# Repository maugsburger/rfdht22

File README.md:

rfdht22
=======

RF temp/hum sensor, grown from a DHT22 and NRF24L01p based sensor to something bigger.

Originally, I just wanted to monitor humidity and temperature in all rooms of my flat, submit them wireless to a master where you can read them out and get some other fancy features (eg close all windows, now it's warmer on the outside than inside).

sensor
------

With every step of hardware design, it grew a little bit bigger, so there are two different version right now:

- either a small headless version with dht22 or one-wire and i2c, powered by attiny2313a, as cheap as possible (single sided with some bridges)

- or a big version with lcd, twi/i2c, one-wire, quad direct analogue and quad opamp driven analogue in

One design goal was to make the sensors as power saving as possible, so they will hopefully run multiple years on a pair of AA cells. No wires, no problem with WAF.

master
------

Power doesn't matter here, big ass display (currently only 4x20 character LCD), can show values of all sensors, and a lot of planned features still in my head.

possible improvements
---------------------

 - lan interface for master
 - hack some radiator controller to enable remote control

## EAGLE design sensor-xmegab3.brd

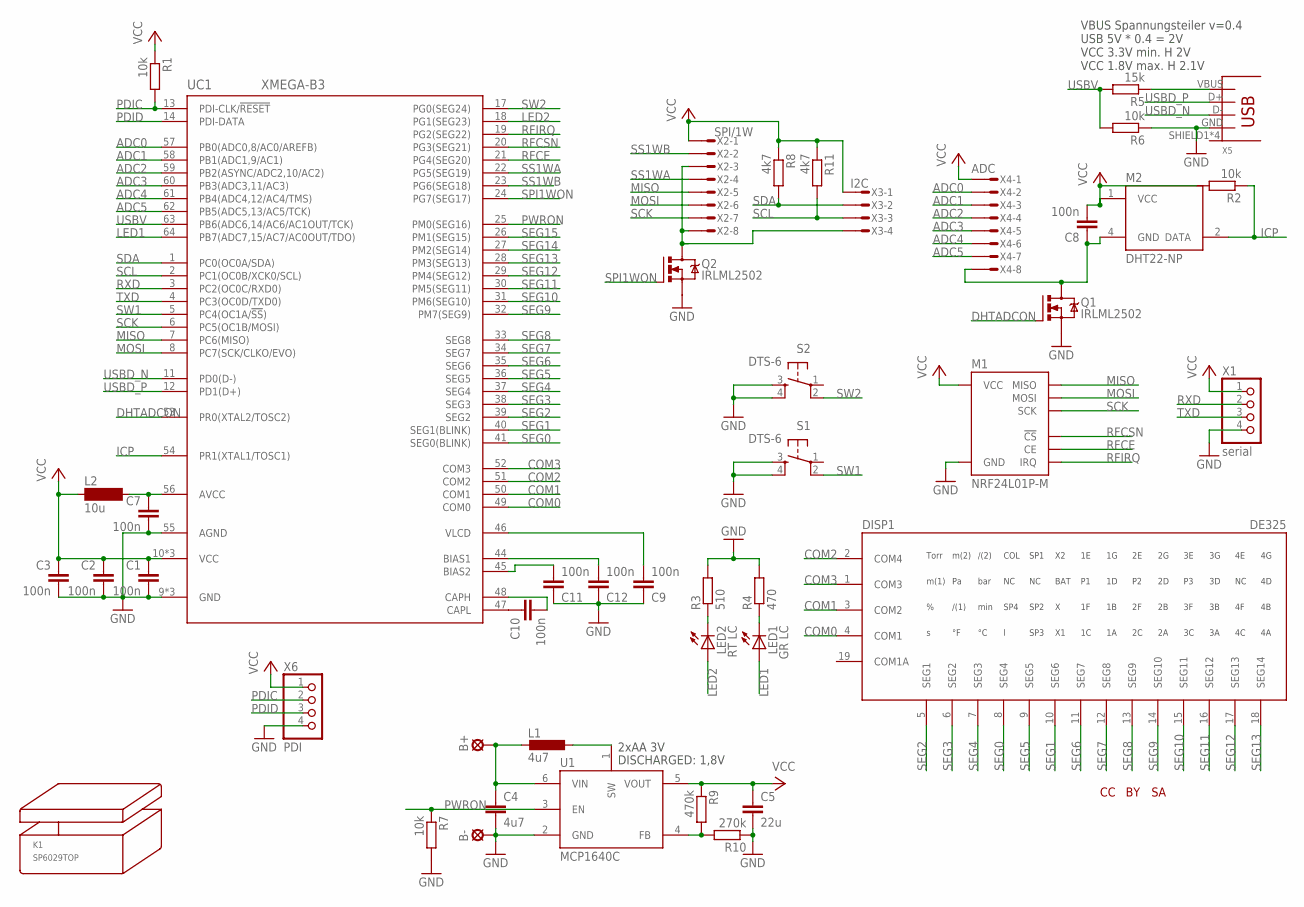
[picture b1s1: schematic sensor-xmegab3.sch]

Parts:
B+: LSP11
B-: LSP11
C1, C2, C3, C7, C8, C9, C10, C11, C12: 100n; C0603
C4: 4u7; C0805
C5: 22u; C1206
DISP1: DE325
K1: SP6029TOP; SP6029T
L1: 4u7; PISG
L2: 10u; SM-NE29
LED1: GR LC; LED5MM
LED2: RT LC; LED5MM
M1: NRF24L01P-M; NRF24L01P-A
M2: DHT22-NP; DHT22-NOPRINT
Q1, Q2: IRLML2502; MICRO3
R1, R2, R6, R7: 10k; R0603
R3: 510; R0805
R4: 470; R0805
R5: 15k; R0603
R8, R11: 4k7; R0603
R9: 470k; R0603
R10: 270k; R0603
S1, S2: DTS-6
U1: MCP1640C; SOT23-6
U$1: CC-TPLACE-HALF; CC_TPLACE_HS
U$3: BY-TPLACE-HS; BY_TPLACE_HS
U$4: SA-TPLACE-HALF; SA_TPLACE_HS
UC1: XMEGA-B3; TQFP64
X1: serial; 1X04
X2: SPI/1W; MICROMATCH-8
X3: I2C; MICROMATCH-4
X4: ADC; MICROMATCH-8
X5: USB; USB-MB-S
X6: PDI; 1X04

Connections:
ADC0: UC1.57 (PB0(ADC0,8/AC0/AREFB)), X4.2
ADC1: UC1.58 (PB1(ADC1,9/AC1)), X4.3
ADC2: UC1.59 (PB2(ASYNC/ADC2,10/AC2)), X4.4
ADC3: UC1.60 (PB3(ADC3,11/AC3)), X4.5
ADC4: UC1.61 (PB4(ADC4,12/AC4/TMS)), X4.6
ADC5: UC1.62 (PB5(ADC5,13/AC5/TCK)), X4.7
AVCC: C7.1, L2.2, UC1.56 (AVCC)
COM0: DISP1.4 (COM1), UC1.49 (COM0)
COM1: DISP1.3 (COM2), UC1.50 (COM1)
COM2: DISP1.2 (COM4), UC1.51 (COM2)
COM3: DISP1.1 (COM3), UC1.52 (COM3)
DHTADCON: Q1.1 (G), UC1.53 (PR0(XTAL2/TOSC2))
GND: B-.MP, C1.2, C2.2, C3.2, C4.2, C5.2, C7.2, C9.1, C11.1, C12.1, M1.GND_A (GND), M1.GND_B (GND), Q1.2 (S), Q2.2 (S), R3.2, R4.2, R6.1, R7.2, R10.1, S1.3, S1.4, S2.3, S2.4, U1.2 (GND), UC1.9 (GND), UC1.15 (GND), UC1.42 (GND), UC1.55 (AGND), X1.4, X5.GND, X6.4
ICP: M2.2 (DATA), R2.1, UC1.54 (PR1(XTAL1/TOSC1))
LED1: LED1.A, UC1.64 (PB7(ADC7,15/AC7/AC0OUT/TDO))
LED2: LED2.A, UC1.18 (PG1(SEG23))
MISO: M1.MISO, UC1.7 (PC6(MISO)), X2.5
MOSI: M1.MOSI, UC1.8 (PC7(SCK/CLKO/EVO)), X2.6
unnamed: LED1.K (C), R4.1
unnamed: R5.1, X5.VBUS
unnamed: LED2.K (C), R3.1
unnamed: L1.1, U1.1 (SW)
unnamed: R9.2, R10.2, U1.4 (FB)
unnamed: C11.2, UC1.45 (BIAS2)
unnamed: C12.2, UC1.44 (BIAS1)
unnamed: Q2.3 (D), X2.3, X2.8, X3.4
unnamed: C8.1, M2.4 (GND), Q1.3 (D), X4.8
unnamed: C9.2, UC1.46 (VLCD)
unnamed: C10.1, UC1.47 (CAPL)
unnamed: C10.2, UC1.48 (CAPH)
PDIC: R1.2, UC1.13 (PDI-CLK/!RESET), X6.2
PDID: UC1.14 (PDI-DATA), X6.3
PWRON: R7.1, U1.3 (EN), UC1.25 (PM0(SEG16))
RFCE: M1.CE, UC1.21 (PG4(SEG20))
RFCSN: M1.CSN (!CS), UC1.20 (PG3(SEG21))
RFIRQ: M1.IRQ, UC1.19 (PG2(SEG22))
RXD: UC1.3 (PC2(OC0C/RXD0)), X1.2
SCK: M1.SCK, UC1.6 (PC5(OC1B/MOSI)), X2.7
SCL: R11.2, UC1.2 (PC1(OC0B/XCK0/SCL)), X3.3
SDA: R8.2, UC1.1 (PC0(OC0A/SDA)), X3.2
SEG0: DISP1.8 (SEG4), UC1.41 (SEG0(BLINK))
SEG1: DISP1.10 (SEG6), UC1.40 (SEG1(BLINK))
SEG2: DISP1.5 (SEG1), UC1.39 (SEG2)
SEG3: DISP1.6 (SEG2), UC1.38 (SEG3)
SEG4: DISP1.7 (SEG3), UC1.37 (SEG4)
SEG5: DISP1.9 (SEG5), UC1.36 (SEG5)
SEG6: DISP1.11 (SEG7), UC1.35 (SEG6)
SEG7: DISP1.12 (SEG8), UC1.34 (SEG7)
SEG8: DISP1.13 (SEG9), UC1.33 (SEG8)
SEG9: DISP1.14 (SEG10), UC1.32 (PM7(SEG9))
SEG10: DISP1.15 (SEG11), UC1.31 (PM6(SEG10))
SEG11: DISP1.16 (SEG12), UC1.30 (PM5(SEG11))
SEG12: DISP1.17 (SEG13), UC1.29 (PM4(SEG12))
SEG13: DISP1.18 (SEG14), UC1.28 (PM3(SEG13))
SEG14: UC1.27 (PM2(SEG14))
SEG15: UC1.26 (PM1(SEG15))
SPI1WON: Q2.1 (G), UC1.24 (PG7(SEG17))
SS1WA: UC1.22 (PG5(SEG19)), X2.4
SS1WB: UC1.23 (PG6(SEG18)), X2.2
SW1: S1.2, UC1.5 (PC4(OC1A/!SS!))
SW2: S2.2, UC1.17 (PG0(SEG24))
TXD: UC1.4 (PC3(OC0D/TXD0)), X1.3
USBD_N: UC1.11 (PD0(D-)), X5.D-
USBD_P: UC1.12 (PD1(D+)), X5.D+
USBV: R5.2, R6.2, UC1.63 (PB6(ADC6,14/AC6/AC1OUT/TCK))
VBAT: B+.MP, C4.1, L1.2, U1.6 (VIN)
VCC: C1.1, C2.1, C3.1, C5.1, C8.2, L2.1, M1.VCC_A (VCC), M1.VCC_B (VCC), M2.1 (VCC), R1.1, R2.2, R8.1, R9.1, R11.1, U1.5 (VOUT), UC1.10 (VCC), UC1.16 (VCC), UC1.43 (VCC), X1.1, X2.1, X3.1, X4.1, X6.1

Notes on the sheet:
2xAA 3V
DISCHARGED: 1,8V
VBUS Spannungsteiler v=0.4 USB 5V * 0.4 = 2V VCC 3.3V min. H 2V VCC 1.8V max. H 2.1V

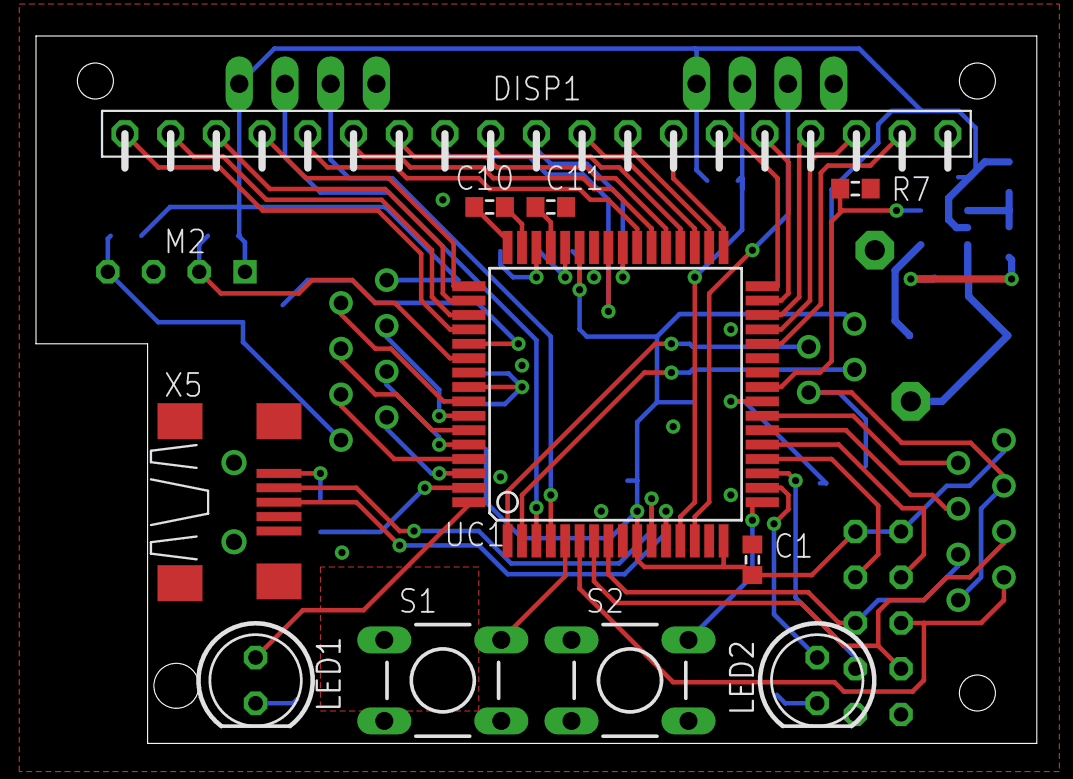
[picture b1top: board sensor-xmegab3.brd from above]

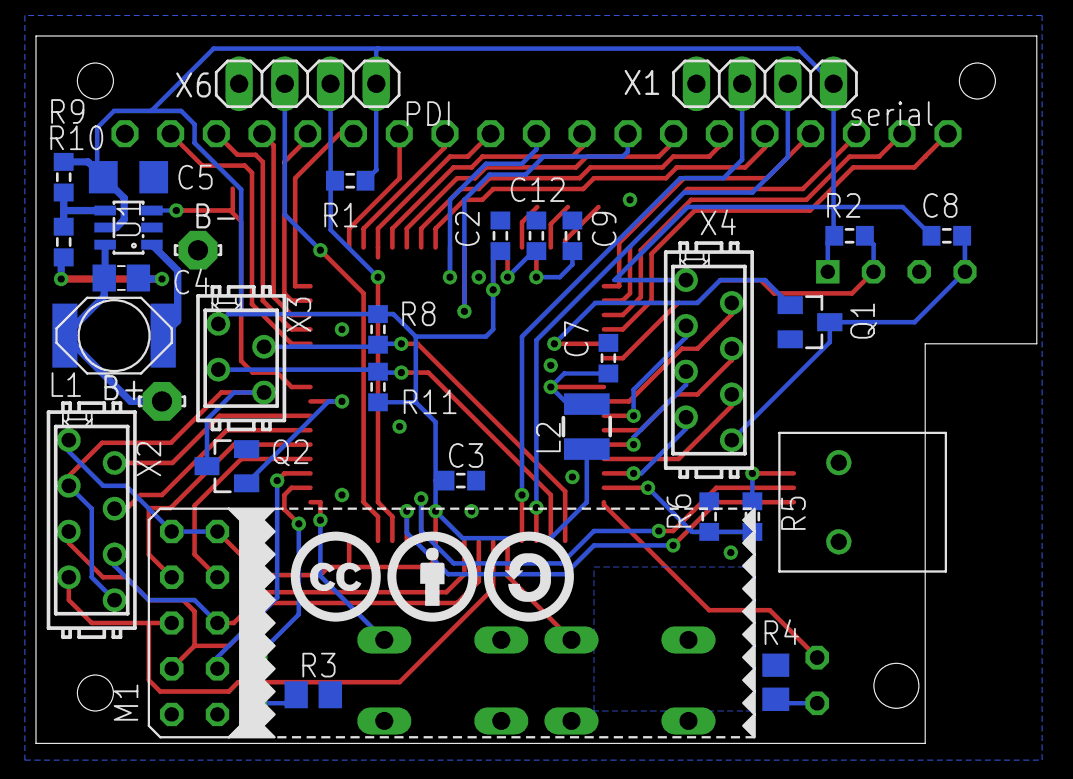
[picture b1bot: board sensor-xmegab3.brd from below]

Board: 2 copper layers, 55.6 x 39.3 mm, 47 parts (34 on the bottom side), 65 nets.

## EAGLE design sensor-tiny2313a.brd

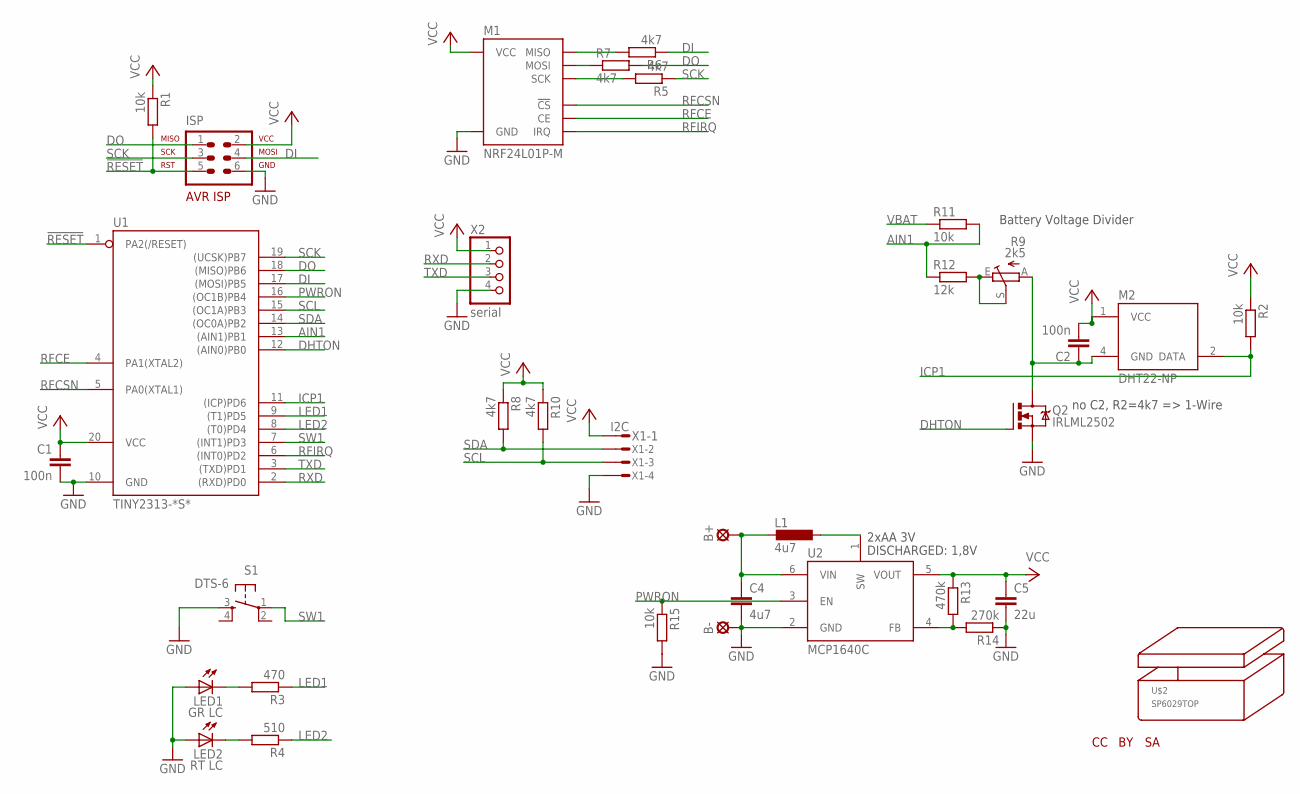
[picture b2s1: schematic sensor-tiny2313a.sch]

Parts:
B+: LSP11
B-: LSP11
C1, C2: 100n; C0603
C4: 4u7; C0805
C5: 22u; C1206
ISP: ML6; AVR-ISP-6
L1: 4u7; PISG
LED1: GR LC; LED5MM
LED2: RT LC; LED5MM
M1: NRF24L01P-M; NRF24L01P-A
M2: DHT22-NP; DHT22-NOPRINT
Q2: IRLML2502; MICRO3
R1, R2, R11, R15: 10k; R0603
R3: 470; R0603
R4: 510; R0603
R5, R6, R7, R8, R10: 4k7; R0603
R9: 2k5; CA6H
R12: 12k; R0603
R13: 470k; R0603
R14: 270k; R0603
S1: DTS-6
U1: TINY2313-*S*; SO20L$
U2: MCP1640C; SOT23-6
U$1: CC-TPLACE-HALF; CC_TPLACE_HS
U$2: SP6029TOP; SP6029T
U$3: BY-TPLACE-HS; BY_TPLACE_HS
U$4: SA-TPLACE-HALF; SA_TPLACE_HS
X1: I2C; MICROMATCH-4
X2: serial; 1X04

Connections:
!RESET: ISP.5, R1.2, U1.1 (PA2(/RESET))
AIN1: R11.2, R12.1, U1.13 ((AIN1)PB1)
DHTON: Q2.1 (G), U1.12 ((AIN0)PB0)
DI: ISP.4, R6.1, U1.17 ((MOSI)PB5)
DO: ISP.1, R7.2, U1.18 ((MISO)PB6)
GND: B-.MP, C1.2, C4.2, C5.2, ISP.6, LED1.A, LED2.A, M1.GND_A (GND), M1.GND_B (GND), Q2.2 (S), R14.1, R15.2, S1.3, U1.10 (GND), U2.2 (GND), X1.4, X2.4
ICP1: M2.2 (DATA), R2.2, U1.11 ((ICP)PD6)
LED1: R3.1, U1.9 ((T1)PD5)
LED2: R4.1, U1.8 ((T0)PD4)
unnamed: LED2.K (C), R4.2
unnamed: C2.1, M2.4 (GND), Q2.3 (D), R9.A
unnamed: LED1.K (C), R3.2
unnamed: R9.E, R9.S, R12.2
unnamed: L1.1, U2.1 (SW)
unnamed: R13.2, R14.2, U2.4 (FB)
PWRON: R15.1, U1.16 ((OC1B)PB4), U2.3 (EN)
RDI: M1.MISO, R6.2
RDO: M1.MOSI, R7.1
RFCE: M1.CE, U1.4 (PA1(XTAL2))
RFCSN: M1.CSN (!CS), U1.5 (PA0(XTAL1))
RFIRQ: M1.IRQ, U1.6 ((INT0)PD2)
RSCK: M1.SCK, R5.2
RXD: U1.2 ((RXD)PD0), X2.2
SCK: ISP.3, R5.1, U1.19 ((UCSK)PB7)
SCL: R10.2, U1.15 ((OC1A)PB3), X1.3
SDA: R8.2, U1.14 ((OC0A)PB2), X1.2
SW1: S1.1, U1.7 ((INT1)PD3)
TXD: U1.3 ((TXD)PD1), X2.3
VBAT: B+.MP, C4.1, L1.2, R11.1, U2.6 (VIN)
VCC: C1.1, C2.2, C5.1, ISP.2, M1.VCC_A (VCC), M1.VCC_B (VCC), M2.1 (VCC), R1.1, R2.1, R8.1, R10.1, R13.1, U1.20 (VCC), U2.5 (VOUT), X1.1, X2.1

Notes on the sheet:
Battery Voltage Divider
2xAA 3V
DISCHARGED: 1,8V
no C2, R2=4k7 => 1-Wire

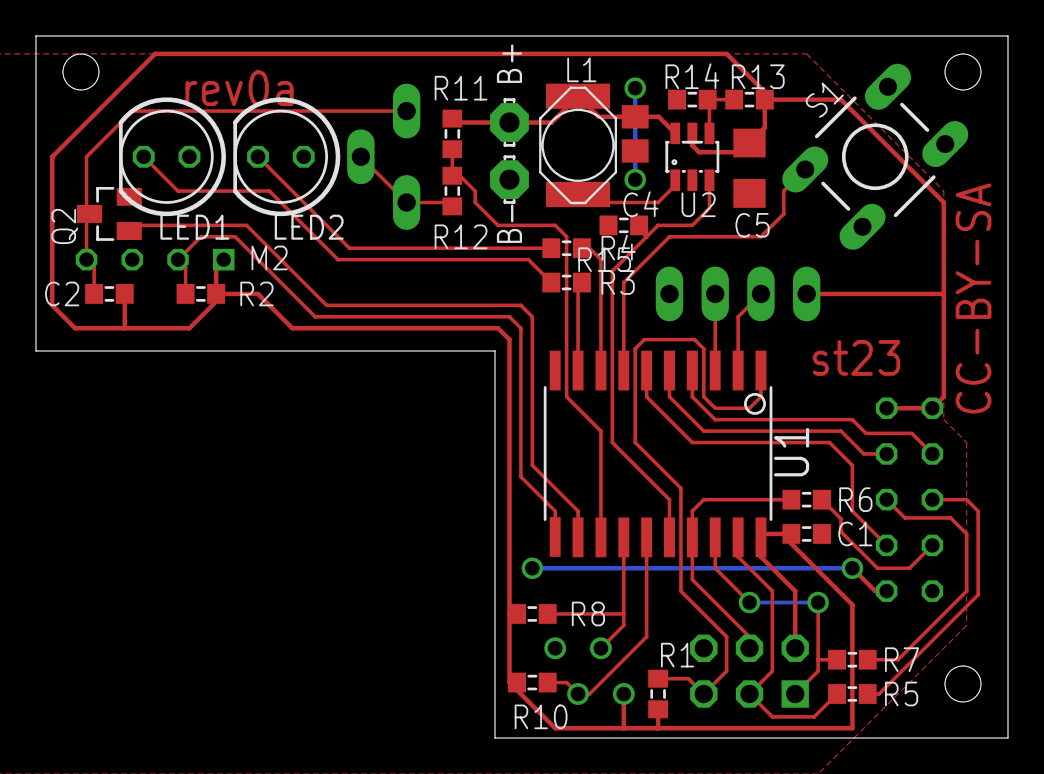
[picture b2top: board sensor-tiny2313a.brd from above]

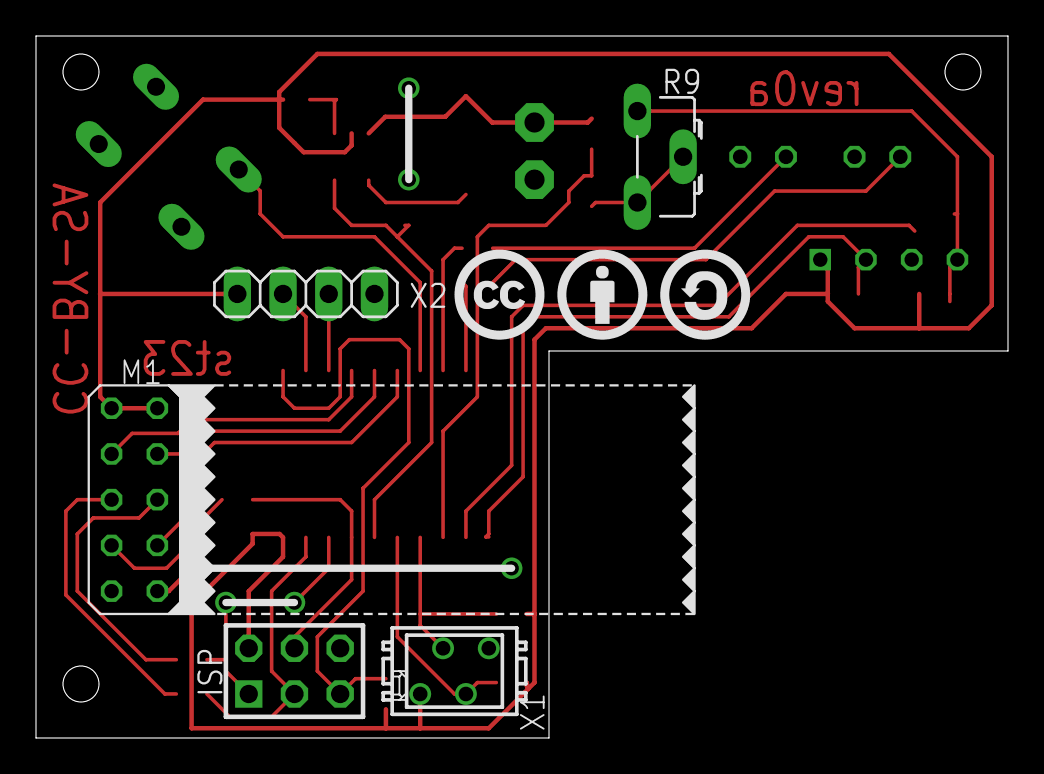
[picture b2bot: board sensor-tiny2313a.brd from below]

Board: 2 copper layers, 54.0 x 39.0 mm, 37 parts (8 on the bottom side), 30 nets.

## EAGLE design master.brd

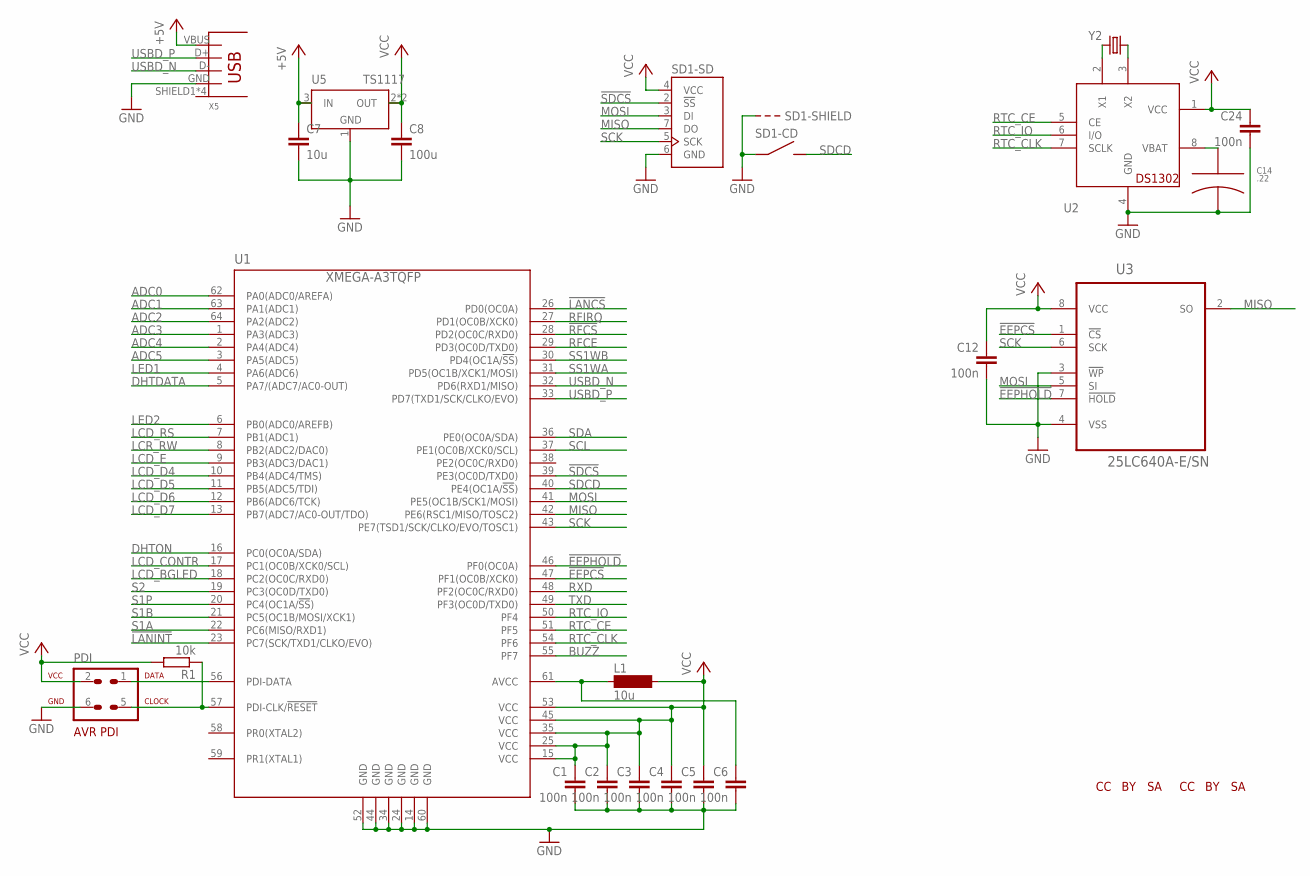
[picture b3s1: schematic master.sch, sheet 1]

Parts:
C1, C2, C3, C4, C5, C6, C12, C24: 100n; C0603
C7: 10u; C1206
C8: 100u; C1210
C14: .22; SUPERCAP
L1: 10u; SM-NE29
PDI: AVR-PDIVERT; AVR-ISP-6
R1: 10k; R0603
SD1: MICROSD_SW; MICROSD_SMD_EXTPIN
U1: XMEGA-A3TQFP; TQFP64
U2: DS1302SOIC; SOIC8_208MIL
U3: 25LC640A-E/SN; SOIC127P600X175-8N
U5: TS1117; SOT223
U$1: CC-TPLACE-HALF; CC_TPLACE_HS
U$2: BY-TPLACE-HS; BY_TPLACE_HS
U$7: SA-TPLACE-HALF; SA_TPLACE_HS
U$8: CC-TOP-HALF; CC_TOP_HS
U$9: BY-TOP-HALF; BY_TOP_HS
U$10: SA-TOP-HALF; SA_TOP_HS
X5: USB-MB-S
Y2: CRYSTALTC26H; TC26H

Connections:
!EEPCS: U1.47 (PF1(OC0B/XCK0)), U3.1 (!CS)
!EEPHOLD: U1.46 (PF0(OC0A)), U3.7 (!HOLD)
!LANCS: U1.26 (PD0(OC0A)); also elsewhere on the board
!LANINT: U1.23 (PC7(SCK/TXD1/CLKO/EVO)); also elsewhere on the board
!RFCS: U1.28 (PD2(OC0C/RXD0)); also elsewhere on the board
!SDCS: SD1.2 (!SS), U1.39 (PE3(OC0D/TXD0))
+5V: C7.1, U5.3 (IN), X5.VBUS; also elsewhere on the board
ADC0: U1.62 (PA0(ADC0/AREFA)); also elsewhere on the board
ADC1: U1.63 (PA1(ADC1)); also elsewhere on the board
ADC2: U1.64 (PA2(ADC2)); also elsewhere on the board
ADC3: U1.1 (PA3(ADC3)); also elsewhere on the board
ADC4: U1.2 (PA4(ADC4)); also elsewhere on the board
ADC5: U1.3 (PA5(ADC5)); also elsewhere on the board
BUZZ: U1.55 (PF7); also elsewhere on the board
DHTDATA: U1.5 (PA7/(ADC7/AC0-OUT)); also elsewhere on the board
DHTON: U1.16 (PC0(OC0A/SDA)); also elsewhere on the board
GND: C1.2, C2.2, C3.2, C4.2, C5.2, C6.2, C7.2, C8.2, C12.2, C14.P$2, C24.2, PDI.6, SD1.6 (GND), SD1.CD1, SD1.NC1 (SHIELD), SD1.NC2 (SHIELD), U1.14 (GND), U1.24 (GND), U1.34 (GND), U1.44 (GND), U1.52 (GND), U1.60 (GND), U2.4 (GND), U3.3 (!WP), U3.4 (VSS), U5.1 (GND), X5.GND; also elsewhere on the board
LCD_BGLED: U1.18 (PC2(OC0C/RXD0)); also elsewhere on the board
LCD_CONTR: U1.17 (PC1(OC0B/XCK0/SCL)); also elsewhere on the board
LCD_D4: U1.10 (PB4(ADC4/TMS)); also elsewhere on the board
LCD_D5: U1.11 (PB5(ADC5/TDI)); also elsewhere on the board
LCD_D6: U1.12 (PB6(ADC6/TCK)); also elsewhere on the board
LCD_D7: U1.13 (PB7(ADC7/AC0-OUT/TDO)); also elsewhere on the board
LCD_E: U1.9 (PB3(ADC3/DAC1)); also elsewhere on the board
LCD_RS: U1.7 (PB1(ADC1)); also elsewhere on the board
LCR_RW: U1.8 (PB2(ADC2/DAC0)); also elsewhere on the board
LED1: U1.4 (PA6(ADC6)); also elsewhere on the board
LED2: U1.6 (PB0(ADC0/AREFB)); also elsewhere on the board
MISO: SD1.7 (DO), U1.42 (PE6(RSC1/MISO/TOSC2)), U3.2 (SO); also elsewhere on the board
MOSI: SD1.3 (DI), U1.41 (PE5(OC1B/SCK1/MOSI)), U3.5 (SI); also elsewhere on the board
unnamed: U2.2 (X1), Y2.2
unnamed: U2.3 (X2), Y2.1
unnamed: C14.P$1, U2.8 (VBAT)
unnamed: PDI.1, U1.56 (PDI-DATA)
unnamed: PDI.5, R1.1, U1.57 (PDI-CLK/!RESET)
unnamed: C6.1, L1.1, U1.61 (AVCC)
RFCE: U1.29 (PD3(OC0D/TXD0)); also elsewhere on the board
RFIRQ: U1.27 (PD1(OC0B/XCK0)); also elsewhere on the board
RTC_CE: U1.51 (PF5), U2.5 (CE)
RTC_CLK: U1.54 (PF6), U2.7 (SCLK)
RTC_IO: U1.50 (PF4), U2.6 (I/O)
RXD: U1.48 (PF2(OC0C/RXD0)); also elsewhere on the board
S1A: U1.22 (PC6(MISO/RXD1)); also elsewhere on the board
S1B: U1.21 (PC5(OC1B/MOSI/XCK1)); also elsewhere on the board
S1P: U1.20 (PC4(OC1A/!SS!)); also elsewhere on the board
S2: U1.19 (PC3(OC0D/TXD0)); also elsewhere on the board
SCK: SD1.5 (SCK), U1.43 (PE7(TSD1/SCK/CLKO/EVO/TOSC1)), U3.6 (SCK); also elsewhere on the board
SCL: U1.37 (PE1(OC0B/XCK0/SCL)); also elsewhere on the board
SDA: U1.36 (PE0(OC0A/SDA)); also elsewhere on the board
SDCD: SD1.CD2, U1.40 (PE4(OC1A/!SS!))
SS1WA: U1.31 (PD5(OC1B/XCK1/MOSI)); also elsewhere on the board
SS1WB: U1.30 (PD4(OC1A/!SS!)); also elsewhere on the board
TXD: U1.49 (PF3(OC0D/TXD0)); also elsewhere on the board
USBD_N: U1.32 (PD6(RXD1/MISO)), X5.D-
USBD_P: U1.33 (PD7(TXD1/SCK/CLKO/EVO)), X5.D+
VCC: C1.1, C2.1, C3.1, C4.1, C5.1, C8.1, C12.1, C24.1, L1.2, PDI.2, R1.2, SD1.4 (VCC), U1.15 (VCC), U1.25 (VCC), U1.35 (VCC), U1.45 (VCC), U1.53 (VCC), U2.1 (VCC), U3.8 (VCC), U5.2 (OUT), U5.4 (OUT); also elsewhere on the board

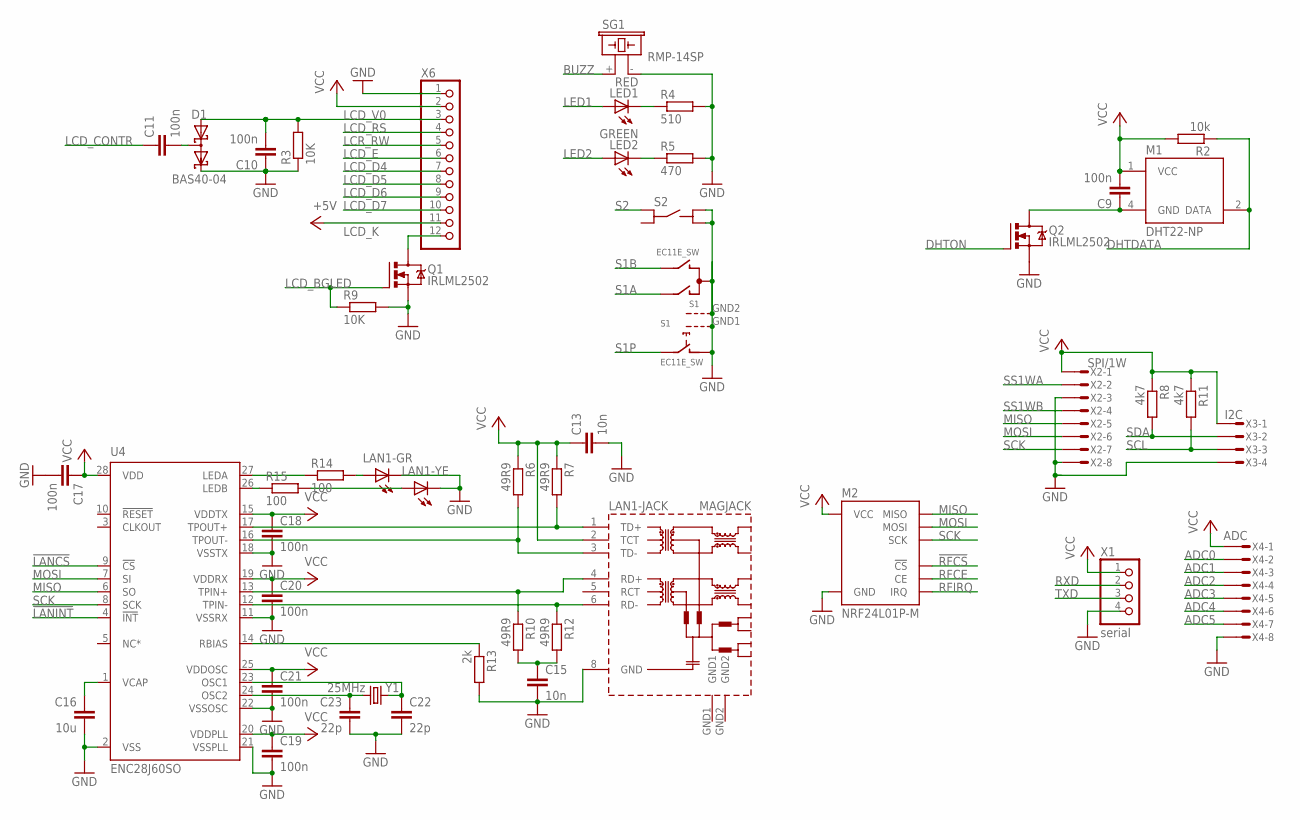
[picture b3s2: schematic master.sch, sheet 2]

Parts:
C9, C10, C11, C17, C18, C19, C20, C21: 100n; C0603
C13, C15: 10n; C0603
C16: 10u; C0603
C22, C23: 22p; C0603
D1: BAS40-04; SOT23
LAN1: MAGJACK
LED1: RED; LED5MM
LED2: GREEN; LED5MM
M1: DHT22-NP; DHT22-NOPRINT
M2: NRF24L01P-M; NRF24L01P-A
Q1, Q2: IRLML2502; MICRO3
R2: 10k; R0603
R3, R9: 10K; R0603
R4: 510; R0603
R5: 470; R0603
R6, R7, R10, R12: 49R9; R0603
R8, R11: 4k7; R0603
R13: 2k; R0603
R14, R15: 100; R0603
S1: EC11E_SW; ALPS_EC11E_SW
S2: MEC-SWITCHSMT; MEC-SMT
SG1: RMP-14SP; F/CM12P
U4: ENC28J60SO; SO28W
X1: serial; 1X04
X2: SPI/1W; MICROMATCH-8
X3: I2C; MICROMATCH-4
X4: ADC; MICROMATCH-8
X6: PINHD-1X12_2.54-R; 1X12R
Y1: 25MHz; HC49/S

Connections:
!LANCS: U4.9 (!CS); also elsewhere on the board
!LANINT: U4.4 (!INT); also elsewhere on the board
!RFCS: M2.CSN (!CS); also elsewhere on the board
+5V: X6.11; also elsewhere on the board
ADC0: X4.2; also elsewhere on the board
ADC1: X4.3; also elsewhere on the board
ADC2: X4.4; also elsewhere on the board
ADC3: X4.5; also elsewhere on the board
ADC4: X4.6; also elsewhere on the board
ADC5: X4.7; also elsewhere on the board
BUZZ: SG1.+ (1); also elsewhere on the board
DHTDATA: M1.2 (DATA), R2.1; also elsewhere on the board
DHTON: Q2.1 (G); also elsewhere on the board
GND: C10.1, C13.2, C15.2, C16.2, C17.2, C18.2, C19.2, C20.2, C21.2, C22.2, C23.2, D1.2 (C2), LAN1.8 (GND), LAN1.LED1.2 (C), LAN1.LED2.2 (C), M2.GND_A (GND), M2.GND_B (GND), Q1.2 (S), Q2.2 (S), R3.1, R4.2, R5.2, R9.2, R13.2, S1.C, S1.D (1), S1.GND1 (G), S1.GND2 (G), S2.3 (B1), S2.4 (B2), SG1.- (2), U4.2 (VSS), U4.11 (VSSRX), U4.18 (VSSTX), U4.21 (VSSPLL), U4.22 (VSSOSC), X1.4, X2.3, X2.8, X3.4, X4.8, X6.1; also elsewhere on the board
LCD_BGLED: Q1.1 (G), R9.1; also elsewhere on the board
LCD_CONTR: C11.1; also elsewhere on the board
LCD_D4: X6.7; also elsewhere on the board
LCD_D5: X6.8; also elsewhere on the board
LCD_D6: X6.9; also elsewhere on the board
LCD_D7: X6.10; also elsewhere on the board
LCD_E: X6.6; also elsewhere on the board
LCD_K: Q1.3 (D), X6.12
LCD_RS: X6.4; also elsewhere on the board
LCD_V0: C10.2, D1.1 (A1), R3.2, X6.3
LCR_RW: X6.5; also elsewhere on the board
LED1: LED1.A; also elsewhere on the board
LED2: LED2.A; also elsewhere on the board
MISO: M2.MISO, U4.6 (SO), X2.5; also elsewhere on the board
MOSI: M2.MOSI, U4.7 (SI), X2.6; also elsewhere on the board
unnamed: LED1.K (C), R4.1
unnamed: C11.2, D1.3 (C1A2)
unnamed: LED2.K (C), R5.1
unnamed: LAN1.4 (RD+), R10.1, U4.13 (TPIN+)
unnamed: C9.1, M1.4 (GND), Q2.3 (D)
unnamed: LAN1.6 (RD-), R12.1, U4.12 (TPIN-)
unnamed: LAN1.3 (TD-), R6.2, U4.16 (TPOUT-)
unnamed: LAN1.1 (TD+), R7.2, U4.17 (TPOUT+)
unnamed: C15.1, R10.2, R12.2
unnamed: R13.1, U4.14 (RBIAS)
unnamed: C23.1, U4.24 (OSC2), Y1.1
unnamed: C22.1, U4.23 (OSC1), Y1.2
unnamed: C16.1, U4.1 (VCAP)
unnamed: R14.1, U4.27 (LEDA)
unnamed: R15.1, U4.26 (LEDB)
unnamed: LAN1.LED2.1 (A), R14.2
unnamed: LAN1.LED1.1 (A), R15.2
RFCE: M2.CE; also elsewhere on the board
RFIRQ: M2.IRQ; also elsewhere on the board
RXD: X1.2; also elsewhere on the board
S1A: S1.A; also elsewhere on the board
S1B: S1.B; also elsewhere on the board
S1P: S1.E (2); also elsewhere on the board
S2: S2.1 (A1); also elsewhere on the board
SCK: M2.SCK, U4.8 (SCK), X2.7; also elsewhere on the board
SCL: R11.2, X3.3; also elsewhere on the board
SDA: R8.2, X3.2; also elsewhere on the board
SS1WA: X2.2; also elsewhere on the board
SS1WB: X2.4; also elsewhere on the board
TXD: X1.3; also elsewhere on the board
VCC: C9.2, C13.1, C17.1, C18.1, C19.1, C20.1, C21.1, LAN1.2 (TCT), M1.1 (VCC), M2.VCC_A (VCC), M2.VCC_B (VCC), R2.2, R6.1, R7.1, R8.1, R11.1, U4.15 (VDDTX), U4.19 (VDDRX), U4.20 (VDDPLL), U4.25 (VDDOSC), U4.28 (VDD), X1.1, X2.1, X3.1, X4.1, X6.2; also elsewhere on the board

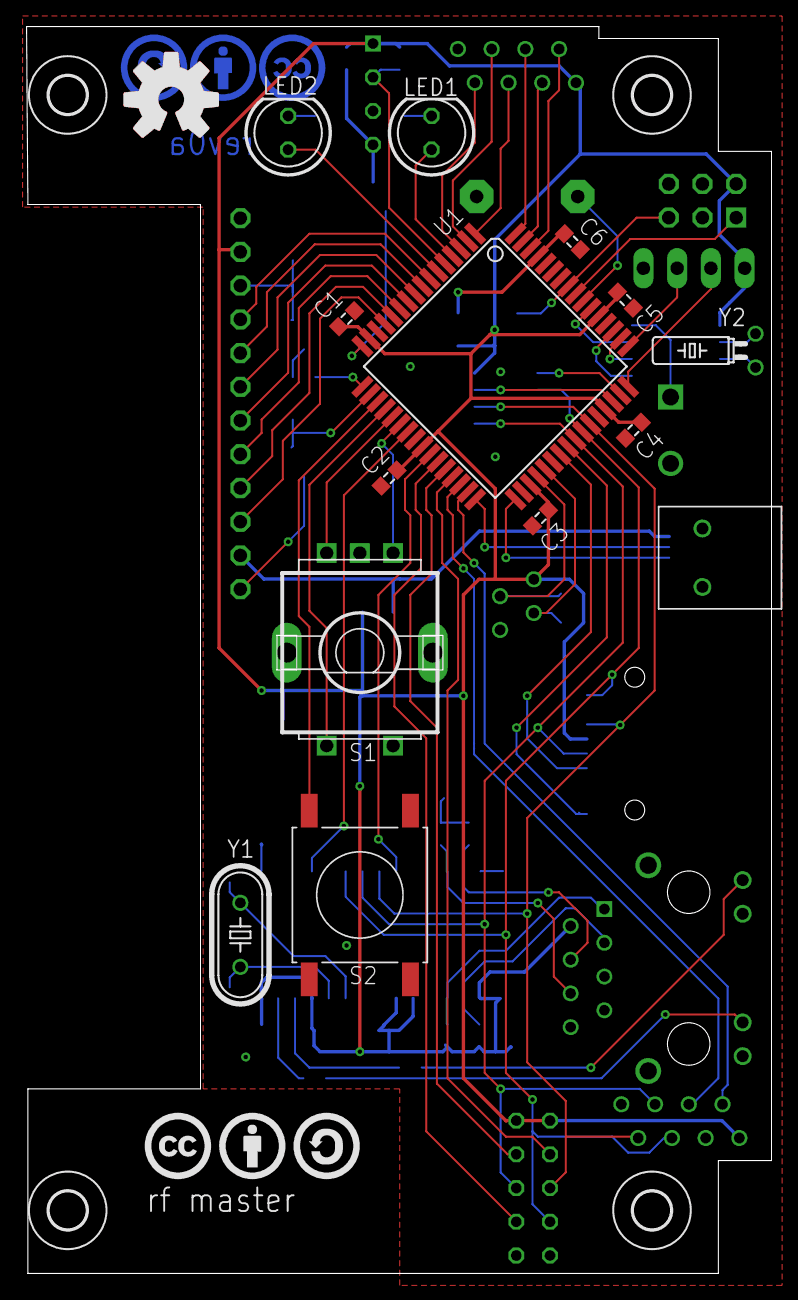
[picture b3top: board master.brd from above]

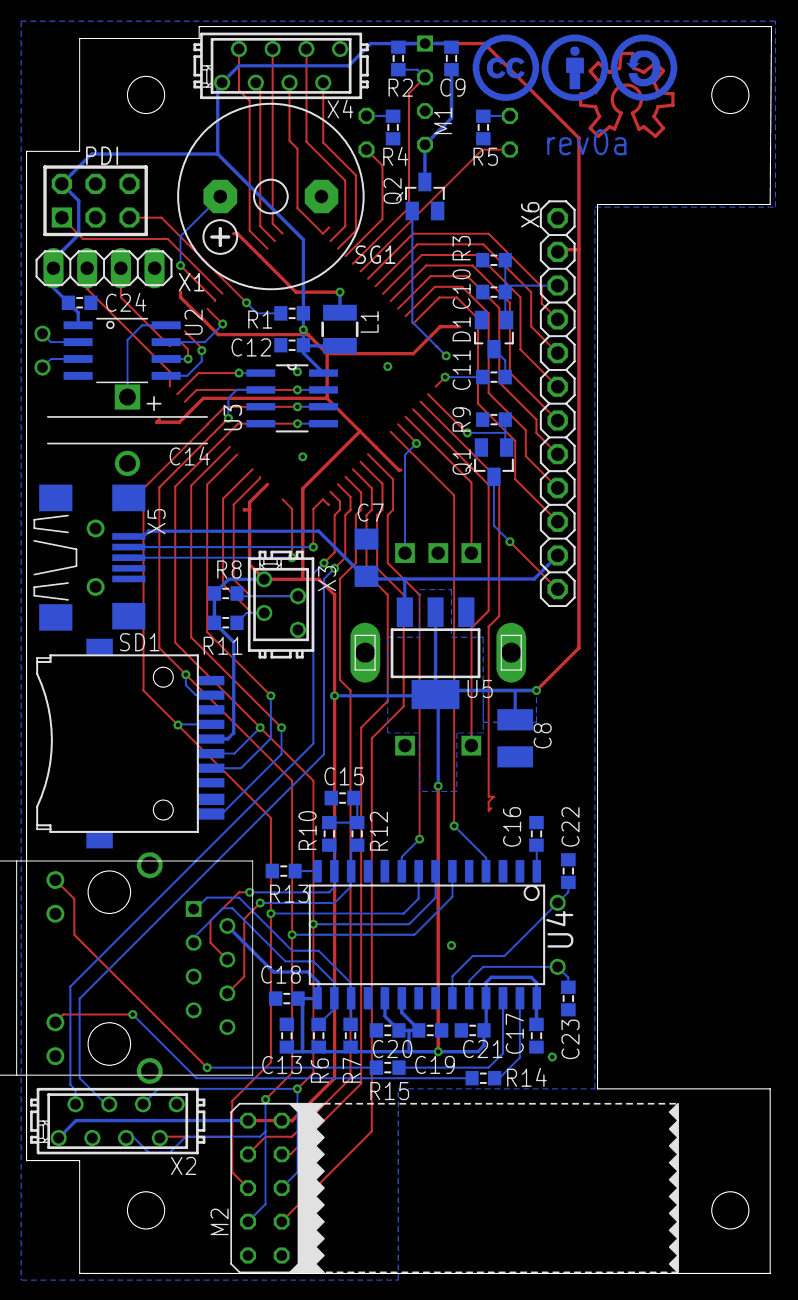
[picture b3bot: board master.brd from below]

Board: 2 copper layers, 56.1 x 93.9 mm, 76 parts (56 on the bottom side), 75 nets.

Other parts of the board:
U$3, U$4, U$5, U$6: 2,8

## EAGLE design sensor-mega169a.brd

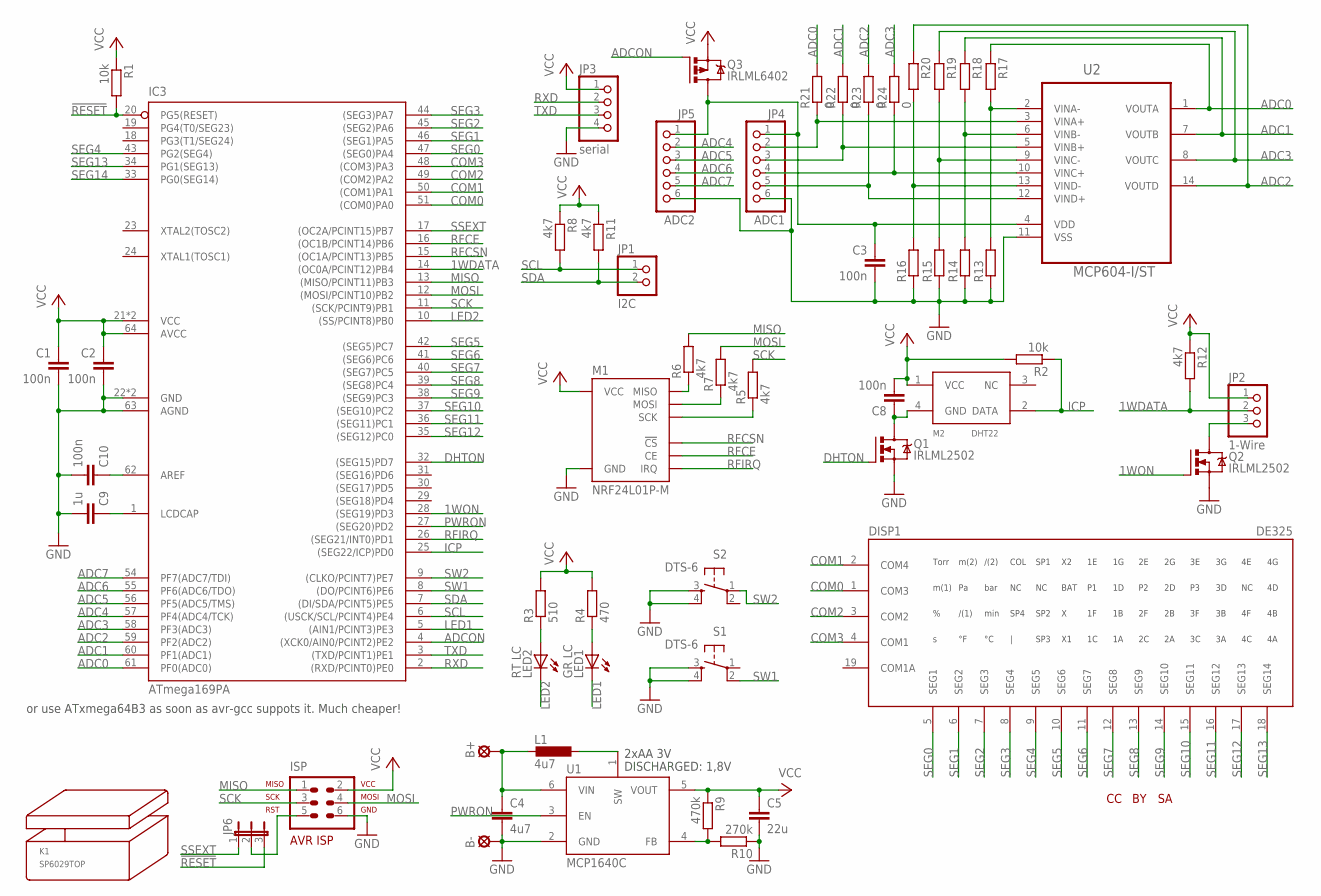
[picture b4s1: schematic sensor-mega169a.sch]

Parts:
B+: LSP11
B-: LSP11
C1, C2, C3, C8, C10: 100n; C0603
C4: 4u7; C0805
C5: 22u; C1206
C9: 1u; C0603
DISP1: DE325
IC3: ATmega169PA; TQFP64
ISP: ML6; AVR-ISP-6
JP1: I2C; 1X02
JP2: 1-Wire; 1X03
JP3: serial; 1X04
JP4: ADC1; 1X06
JP5: ADC2; 1X06
JP6: JP2E; JP2
K1: SP6029TOP; SP6029T
L1: 4u7; PISG
LED1: GR LC; LED5MM
LED2: RT LC; LED5MM
M1: NRF24L01P-M; NRF24L01P-A
M2: DHT22
Q1, Q2: IRLML2502; MICRO3
Q3: IRLML6402; MICRO3
R1, R2: 10k; R0603
R3: 510; R0805
R4: 470; R0805
R5, R6, R7, R8, R11, R12: 4k7; R0603
R9: 470k; R0603
R10: 270k; R0603
R13, R14, R15, R16, R17, R18, R19, R20: R-EU_R0603; R0603
R21, R22, R23, R24: 0; R0201
S1, S2: DTS-6
U1: MCP1640C; SOT23-6
U2: MCP604-I/ST; SOP65P640X120-14N
U$1: CC-TPLACE-HALF; CC_TPLACE_HS
U$3: BY-TPLACE-HS; BY_TPLACE_HS
U$4: SA-TPLACE-HALF; SA_TPLACE_HS

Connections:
1WDATA: IC3.14 ((OC0A/PCINT12)PB4), JP2.2, R12.2
1WON: IC3.28 ((SEG19)PD3), Q2.1 (G)
!RESET: IC3.20 (PG5(RESET)), JP6.3, R1.2
ADC0: IC3.61 (PF0(ADC0)), R17.1, R21.2, U2.1 (VOUTA)
ADC1: IC3.60 (PF1(ADC1)), R18.1, R22.2, U2.7 (VOUTB)
ADC2: IC3.59 (PF2(ADC2)), R20.1, R23.2, U2.14 (VOUTD)
ADC3: IC3.58 (PF3(ADC3)), R19.1, R24.2, U2.8 (VOUTC)
ADC4: IC3.57 (PF4(ADC4/TCK)), JP5.2
ADC5: IC3.56 (PF5(ADC5/TMS)), JP5.3
ADC6: IC3.55 (PF6(ADC6/TDO)), JP5.4
ADC7: IC3.54 (PF7(ADC7/TDI)), JP5.5
ADCON: IC3.4 ((XCK0/AIN0/PCINT2)PE2), Q3.1 (G)
AREF: C10.1, IC3.62 (AREF)
COM0: DISP1.1 (COM3), IC3.51 ((COM0)PA0)
COM1: DISP1.2 (COM4), IC3.50 ((COM1)PA1)
COM2: DISP1.3 (COM2), IC3.49 ((COM2)PA2)
COM3: DISP1.4 (COM1), IC3.48 ((COM3)PA3)
DHTON: IC3.32 ((SEG15)PD7), Q1.1 (G)
GND: B-.MP, C1.2, C2.2, C3.2, C4.2, C5.2, C9.2, C10.2, IC3.22 (GND), IC3.53 (GND), IC3.63 (AGND), ISP.6, JP3.4, JP4.6, JP5.6, M1.GND_A (GND), M1.GND_B (GND), Q1.2 (S), Q2.2 (S), R10.1, R13.1, R14.1, R15.1, R16.1, S1.3, S1.4, S2.3, S2.4, U1.2 (GND), U2.11 (VSS)
ICP: IC3.25 ((SEG22/ICP)PD0), M2.2 (DATA), R2.1
LCDCAP: C9.1, IC3.1 (LCDCAP)
LED1: IC3.5 ((AIN1/PCINT3)PE3), LED1.K (C)
LED2: IC3.10 ((SS/PCINT8)PB0), LED2.K (C)
MISO: IC3.13 ((MISO/PCINT11)PB3), ISP.1, R6.2
MOSI: IC3.12 ((MOSI/PCINT10)PB2), ISP.4, R7.2
unnamed: LED2.A, R3.1
unnamed: C8.1, M2.4 (GND), Q1.3 (D)
unnamed: M1.MISO, R6.1
unnamed: M1.MOSI, R7.1
unnamed: M1.SCK, R5.1
unnamed: ISP.5, JP6.2
unnamed: L1.1, U1.1 (SW)
unnamed: R9.2, R10.2, U1.4 (FB)
unnamed: JP2.3, Q2.3 (D)
unnamed: LED1.A, R4.1
unnamed: JP4.2, R21.1, U2.3 (VINA+)
unnamed: C3.1, JP4.1, JP5.1, Q3.3 (D), U2.4 (VDD)
unnamed: R16.2, R20.2, U2.13 (VIND-)
unnamed: R15.2, R19.2, U2.9 (VINC-)
unnamed: R14.2, R18.2, U2.6 (VINB-)
unnamed: R13.2, R17.2, U2.2 (VINA-)
unnamed: JP4.3, R22.1, U2.5 (VINB+)
unnamed: JP4.5, R23.1, U2.12 (VIND+)
unnamed: JP4.4, R24.1, U2.10 (VINC+)
PWRON: IC3.27 ((SEG20)PD2), U1.3 (EN)
RFCE: IC3.16 ((OC1B/PCINT14)PB6), M1.CE
RFCSN: IC3.15 ((OC1A/PCINT13)PB5), M1.CSN (!CS)
RFIRQ: IC3.26 ((SEG21/INT0)PD1), M1.IRQ
RXD: IC3.2 ((RXD/PCINT0)PE0), JP3.2
SCK: IC3.11 ((SCK/PCINT9)PB1), ISP.3, R5.2
SCL: IC3.6 ((USCK/SCL/PCINT4)PE4), JP1.1, R8.2
SDA: IC3.7 ((DI/SDA/PCINT5)PE5), JP1.2, R11.2
SEG0: DISP1.5 (SEG1), IC3.47 ((SEG0)PA4)
SEG1: DISP1.6 (SEG2), IC3.46 ((SEG1)PA5)
SEG2: DISP1.7 (SEG3), IC3.45 ((SEG2)PA6)
SEG3: DISP1.8 (SEG4), IC3.44 ((SEG3)PA7)
SEG4: DISP1.9 (SEG5), IC3.43 (PG2(SEG4))
SEG5: DISP1.10 (SEG6), IC3.42 ((SEG5)PC7)
SEG6: DISP1.11 (SEG7), IC3.41 ((SEG6)PC6)
SEG7: DISP1.12 (SEG8), IC3.40 ((SEG7)PC5)
SEG8: DISP1.13 (SEG9), IC3.39 ((SEG8)PC4)
SEG9: DISP1.14 (SEG10), IC3.38 ((SEG9)PC3)
SEG10: DISP1.15 (SEG11), IC3.37 ((SEG10)PC2)
SEG11: DISP1.16 (SEG12), IC3.36 ((SEG11)PC1)
SEG12: DISP1.17 (SEG13), IC3.35 ((SEG12)PC0)
SEG13: DISP1.18 (SEG14), IC3.34 (PG1(SEG13))
SEG14: IC3.33 (PG0(SEG14))
SSEXT: IC3.17 ((OC2A/PCINT15)PB7), JP6.1
SW1: IC3.8 ((DO/PCINT6)PE6), S1.2
SW2: IC3.9 ((CLKO/PCINT7)PE7), S2.1
TXD: IC3.3 ((TXD/PCINT1)PE1), JP3.3
VBAT: B+.MP, C4.1, L1.2, U1.6 (VIN)
VCC: C1.1, C2.1, C5.1, C8.2, IC3.21 (VCC), IC3.52 (VCC), IC3.64 (AVCC), ISP.2, JP2.1, JP3.1, M1.VCC_A (VCC), M1.VCC_B (VCC), M2.1 (VCC), Q3.2 (S), R1.1, R2.2, R3.2, R4.2, R8.1, R9.1, R11.1, R12.1, U1.5 (VOUT)

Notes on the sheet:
2xAA 3V
DISCHARGED: 1,8V
or use ATxmega64B3 as soon as avr-gcc suppots it. Much cheaper!

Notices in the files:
parts and their libraries:
creative-commons: creative commons
Attribution - BY
